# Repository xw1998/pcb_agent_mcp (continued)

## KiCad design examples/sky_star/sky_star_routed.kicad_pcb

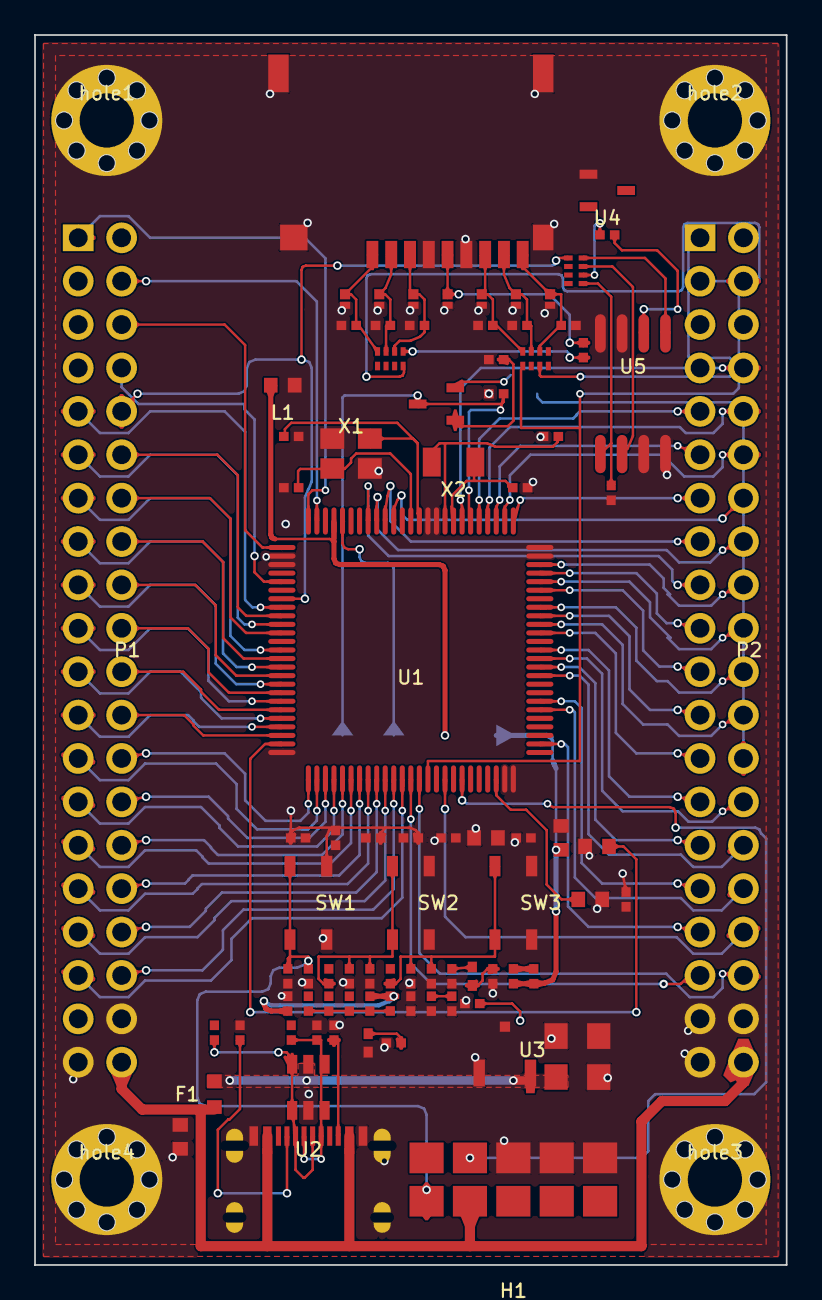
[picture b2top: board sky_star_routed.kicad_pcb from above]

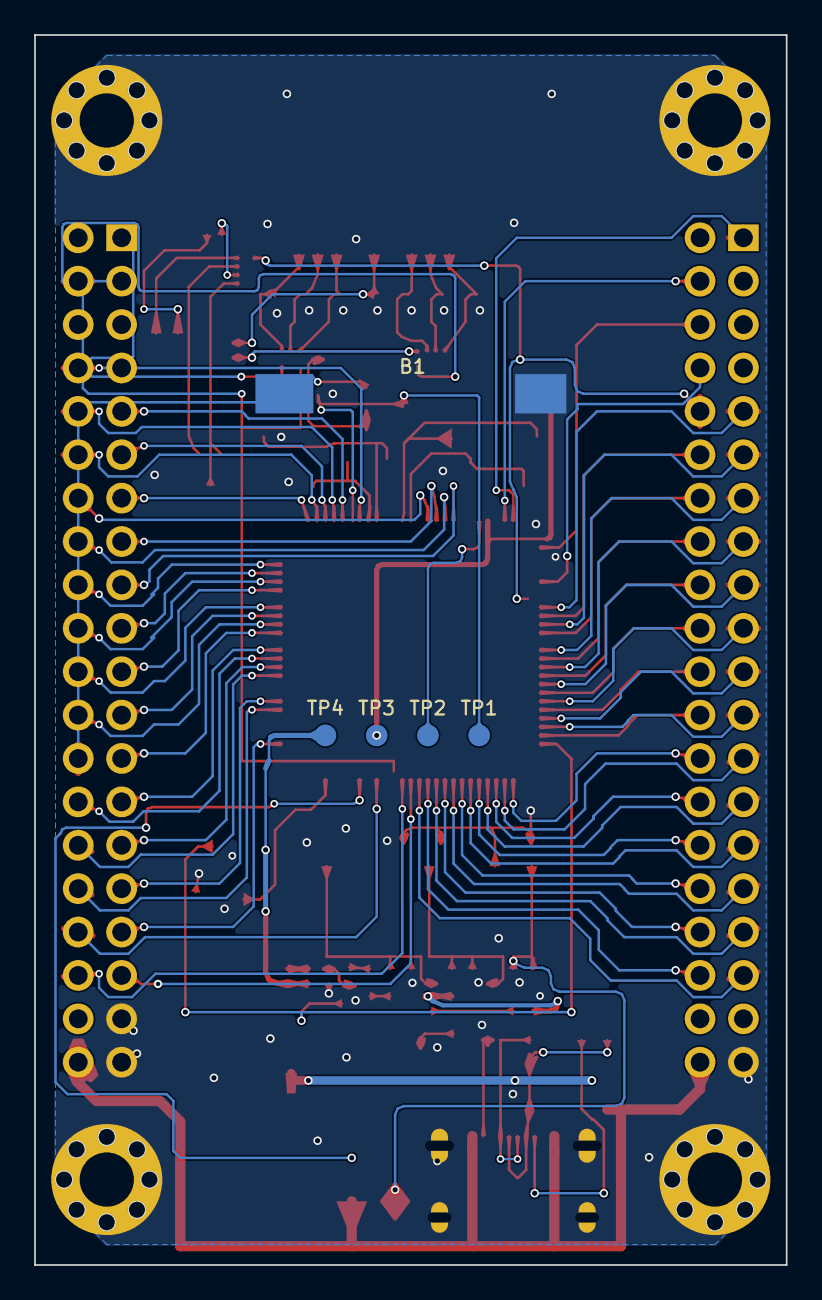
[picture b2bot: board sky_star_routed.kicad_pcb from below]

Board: 2 copper layers, 44.0 x 72.0 mm, 96 parts (5 on the bottom side), 120 nets.

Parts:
B1: 61b387a3f8cf4f8cb9003285; B1
C1: 898d0016e41540f8ae025366; C1
C2: 898d0016e41540f8ae025366; C2
C3: a80f3ac1373c41b29e79f8ac; C3
C4: a80f3ac1373c41b29e79f8ac; C4
C5: ba92d279d25f4ddfba864fc3; C5
C6: 985a7bbf505b401b9df199a7; C6
C7: 985a7bbf505b401b9df199a7; C7
C8: 503038ece5c945bd836f8146; C8
C9: 503038ece5c945bd836f8146; C9
C10: ba92d279d25f4ddfba864fc3; C10
C11: 985a7bbf505b401b9df199a7; C11
C12: 674f7d04ecfe47e19e31325e; C12
C13: 985a7bbf505b401b9df199a7; C13
C14: 985a7bbf505b401b9df199a7; C14
C15: 985a7bbf505b401b9df199a7; C15
C16: 985a7bbf505b401b9df199a7; C16
C17: 985a7bbf505b401b9df199a7; C17
C18: 985a7bbf505b401b9df199a7; C18
C19: c3d1642f07c74a079740bc29; C19
C20: c3d1642f07c74a079740bc29; C20
C21: ed38a11610a64051a2e5fa8d; C21
C22: 674f7d04ecfe47e19e31325e; C22
C23: 985a7bbf505b401b9df199a7; C23
C24: 985a7bbf505b401b9df199a7; C24
C25: 985a7bbf505b401b9df199a7; C25
C26: 985a7bbf505b401b9df199a7; C26
C27: 985a7bbf505b401b9df199a7; C27
CARD1: 0e7a72cfa4f643628d5d1c22; CARD1
D1: d04567a3f4bd40c58faa9031; D1
D2: e103e84b8c7c4680b01127bb; D2
D3: 9a006e8efdae40648d5732ff; D3
D4: 9a006e8efdae40648d5732ff; D4
D5: 9a006e8efdae40648d5732ff; D5
D6: 9a006e8efdae40648d5732ff; D6
D7: 9a006e8efdae40648d5732ff; D7
D8: 9a006e8efdae40648d5732ff; D8
D9: 9a006e8efdae40648d5732ff; D9
F1: b4abf8c794e84f298081ad3d; F1
H1: e0b313ac55d14cdd8e1d890f; H1
L1: c4be498a9b2c478d9cc6793a; L1
LED1: b2f59cdef59d49788923a43d; LED1
LED2: d5cfa2539fc44cb2b9e9363e; LED2
P1: 62604d02a0e44089874c6f57; P1
P2: 62604d02a0e44089874c6f57; P2
R1: 12b2efa1cf58486a9619da63; R1
R2: 12b2efa1cf58486a9619da63; R2
R3: 12b2efa1cf58486a9619da63; R3
R4: ec8dbb3ef10a4b60836874c1; R4
R5: 12b2efa1cf58486a9619da63; R5
R6: 12b2efa1cf58486a9619da63; R6
R7: 12b2efa1cf58486a9619da63; R7
R8: 12b2efa1cf58486a9619da63; R8
R9: 3798b972c8914680bf389273; R9
R10: 7d8c83fa2ece4dc88e778541; R10
R11: 7d8c83fa2ece4dc88e778541; R11
R12: 3798b972c8914680bf389273; R12
R13: d347a19dff4940ed89f0538a; R13
R14: 8adac930023d4a0e80259176; R14
R15: 41c2377d4d534296a53042e6; R15
R16: 41c2377d4d534296a53042e6; R16
R17: 41c2377d4d534296a53042e6; R17
R18: 41c2377d4d534296a53042e6; R18
R19: 41c2377d4d534296a53042e6; R19
R20: 41c2377d4d534296a53042e6; R20
R21: 203e7d3950e0483ab1e27f5d; R21
R22: 8d212afd70d04d809b7d3a37; R22
R23: 203e7d3950e0483ab1e27f5d; R23
R24: faff0499d77046cc8d3395ba; R24
R25: faff0499d77046cc8d3395ba; R25
R26: faff0499d77046cc8d3395ba; R26
R27: faff0499d77046cc8d3395ba; R27
R28: faff0499d77046cc8d3395ba; R28
R29: 8adac930023d4a0e80259176; R29
R30: faff0499d77046cc8d3395ba; R30
RN1: 03d8c6fff59145c59e14821e; RN1
RN2: 03d8c6fff59145c59e14821e; RN2
RN3: 03d8c6fff59145c59e14821e; RN3
SW1: 8a353f60d85b4c9a8f6ee1d9; SW1
SW2: 0186f8a51cea40f9996dc1e2; SW2
SW3: 0186f8a51cea40f9996dc1e2; SW3
TP1: 307121d53d324ab8bbacd7b3; TP1
TP2: 307121d53d324ab8bbacd7b3; TP2
TP3: 307121d53d324ab8bbacd7b3; TP3
TP4: 307121d53d324ab8bbacd7b3; TP4
U1: e9bc99d2d5884074a910997b; U1
U2: 05cba19d26b44aca94b25e1e; U2
U3: dfcfb6bb46c94cd29580c5ab; U3
U4: 13454547d96d49deb0b2d1d6; U4
U5: 0725a72de06845509f1a35bc; U5
X1: 833c1e2704e6450da98a095b; X1
X2: 3dc4ad2b372549639630adff; X2
hole1: b4e398820e034dc2a8638f46; hole1
hole2: b4e398820e034dc2a8638f46; hole2
hole3: b4e398820e034dc2a8638f46; hole3
hole4: b4e398820e034dc2a8638f46; hole4

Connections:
$1I5653/$1N710: C26.2, R25.2, R27.1, SW2.3, SW2.4
$1I5653/$1N718: C27.2, R26.2, R28.1, SW3.3, SW3.4
$1I5653/$1N747: LED2.1, R29.1
$1I7801/$1N957: R11.1, U2.B5
$1I7801/$1N960: R10.1, U2.A5
$1I7801/$1N962: D2.1, D2.6, R9.1, U2.A7, U2.B7
$1I7801/$1N2108: LED1.1, R14.1
$1I7801/$1N8196: D2.3, D2.4, R12.1, R13.1, U2.A6, U2.B6
$1I7895/$1N1161: CARD1.5, D9.1, R21.2
$1I7895/$1N1206: R23.1, U5.6
$1I7895/_SDIO_CLK: R21.1, RN1.4
$1I7895/_SDIO_CMD: CARD1.3, D8.1, R15.1, RN1.3
$1I7895/_SDIO_D0: CARD1.7, D7.1, R16.1, RN2.1
$1I7895/_SDIO_D1: CARD1.8, D6.1, R17.1, RN2.2
$1I7895/_SDIO_D2: CARD1.1, D5.1, R18.1, RN1.1
$1I7895/_SDIO_D3: CARD1.2, D4.1, R19.1, RN1.2
$1I7895/_SD_CARD_DET: CARD1.9, D3.1, R20.1, RN2.3
$1I7895/_SPI_CLK: R23.2, RN3.3
$1I7895/_SPI_CS: R22.1, RN3.4, U5.1
$1I7895/_SPI_MISO: RN3.2, U5.2
$1I7895/_SPI_MOSI: RN3.1, U5.5
$1I8749/$2N1173: C7.1, D1.3, TP1.1, U1.6
$1I8749/$2N1176: D1.1, R3.2
$1I8749/$2N1188: C5.1, C6.2, R1.1, R2.1, R4.1, TP2.1, U1.21
$1I8749/$2N1193: C8.2, U1.73
$1I8749/$2N1197: R5.2, R6.2, U1.19
$1I8749/$2N1200: C9.2, R7.2, U1.49
$1I8749/OSC32_IN: C3.2, U1.8, X2.1
$1I8749/OSC32_OUT: C4.2, U1.9, X2.2
$1I8749/OSC_IN: C2.1, U1.12, X1.3
$1I8749/OSC_OUT: C1.2, U1.13, X1.1
$1I8749/VDDA: C10.2, C11.2, L1.2, R4.2, TP3.1, U1.22
$1N4349: R26.1, U1.94
$1N4351: LED2.2, R30.1, U1.37
$1N4401: H1.8, U1.69
$1N4403: H1.10, U1.68
$1N4405: H1.3, U1.76
$1N4407: H1.5, U1.72
$1N4409: H1.1, U1.89
$1N4415: C25.2, H1.9, R24.2, SW1.3, SW1.4, U1.14
$1N4746: P2.33, U1.77
$1N4748: P1.11, U1.35
$1N4750: P1.14, U1.36
$1N4752: P2.8, U1.7
$1N4754: P2.32, U1.81
$1N4756: P2.31, U1.82
$1N4758: P2.34, U1.67
$1N4760: P1.2, R2.2
$1N4849: P2.4, RN1.5, U1.80
$1N4856: P2.5, RN1.6, U1.83
$1N4863: P2.3, RN2.8, U1.65
$1N4870: P2.2, RN2.7, U1.66
$1N4877: P2.7, RN1.8, U1.78
$1N4884: P2.6, RN1.7, U1.79
$1N4891: P2.1, RN2.6, U1.84
$1N4898: P1.5, RN3.5, U1.29
$1N4905: P1.8, RN3.6, U1.30
$1N4912: P1.7, RN3.7, U1.31
$1N4919: P1.10, RN3.8, U1.32
$1N5556: R1.2, U4.2
$1N5560: R9.2, U1.70
$1N5562: R12.2, U1.71
$1N8183: P1.3, R25.1, U1.23
$1N9171: B1.1, D1.2, P2.26
+3V3: C12.2, C13.2, C14.2, C15.2, C16.2, C17.2, C18.2, C20.1, C21.2, C22.1, C23.1, C24.2, C26.1, C27.1, CARD1.4, H1.2, L1.1, LED1.2, P1.38, P2.38, R3.1, R5.1, R13.2, R15.2, R16.2, R17.2, R18.2, R19.2, R20.2, R22.2, R24.1, SW2.1, SW2.2, SW3.1, SW3.2, U1.11, U1.28, U1.50, U1.75, U1.100, U3.2, U4.1, U5.3, U5.7, U5.8
+5V: C19.1, D2.5, F1.2, U3.3
AGND: C5.2, C6.1, C10.1, C11.1, C21.1, P1.37, R8.1, TP4.1, U1.20, U4.3
GND: B1.2, C1.1, C2.2, C3.1, C4.1, C7.2, C8.1, C9.1, C12.1, C13.1, C14.1, C15.1, C16.1, C17.1, C18.1, C19.2, C20.2, C22.2, C23.2, C24.1, C25.1, CARD1.6, CARD1.10, CARD1.11, CARD1.12, CARD1.13, D2.2, D3.2, D4.2, D5.2, D6.2, D7.2, D8.2, D9.2, H1.4, H1.6, P1.39, P2.37, P2.39, R6.1, R7.1, R8.2, R10.2, R11.2, R14.2, R27.2, R28.2, R29.2, R30.2, SW1.1, SW1.2, U1.10, U1.27, U1.74, U1.99, U2.1, U2.2, U2.3, U2.4, U2.A1B12, U2.A12B1, U3.1, U5.4, X1.2, X1.4, hole1.1, hole2.1, hole3.1, hole4.1
PA1: P1.4, U1.24
PA2: P1.1, U1.25
PA3: P1.6, U1.26
PB4: P2.25, U1.90
PB5: P2.24, U1.91
PB6: P2.23, U1.92
PB7: P2.22, U1.93
PB8: P2.21, U1.95
PB9: P2.20, U1.96
PB10: P1.23, U1.47
PB11: P1.24, U1.48
PB12: P1.26, U1.51
PB13: P1.25, U1.52
PB14: P1.28, U1.53
PB15: P1.27, U1.54
PC0: P2.14, U1.15
PC1: P2.15, U1.16
PC2: P2.16, U1.17
PC3: P2.17, U1.18
PC4: P1.9, U1.33
PC5: P1.12, U1.34
PC6: P2.35, U1.63
PC7: P2.36, U1.64
PD4: P2.30, U1.85
PD5: P2.29, U1.86
PD6: P2.28, U1.87
PD7: P2.27, U1.88
PD8: P1.30, U1.55
PD9: P1.29, U1.56
PD10: P1.32, U1.57
PD11: P1.31, U1.58
PD12: P1.34, U1.59
PD13: P1.33, U1.60
PD14: P1.36, U1.61
PD15: P1.35, U1.62
PE0: P2.19, U1.97
PE1: P2.18, U1.98
PE2: P2.13, U1.1
PE3: P2.12, U1.2
PE4: P2.11, U1.3
PE5: P2.10, U1.4
PE6: P2.9, U1.5
PE7: P1.13, U1.38
PE8: P1.16, U1.39
PE9: P1.15, U1.40
PE10: P1.18, U1.41
PE11: P1.17, U1.42
PE12: P1.20, U1.43
PE13: P1.19, U1.44
PE14: P1.22, U1.45
PE15: P1.21, U1.46
PIN_IN_+5V: F1.1, H1.7, P1.40, P2.40, U2.A4B9, U2.A9B4

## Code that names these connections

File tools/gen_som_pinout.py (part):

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EDGES = {
    # ---- N：RGB LCDC 28 信号（VO_LCDC_D0..D23 + CLK/HSYNC/VSYNC/DEN）
    "N": [
        ("sig", "G3", "LCDC_D0", "GPIO1/LCDC"),
        ("sig", "F2", "LCDC_D1", "GPIO1/LCDC"),
        ("sig", "F3", "LCDC_D2", "GPIO1/LCDC"),
        ("sig", "E1", "LCDC_D3", "GPIO1/LCDC"),
        ("sig", "E2", "LCDC_D4", "GPIO1/LCDC"),
        ("sig", "E3", "LCDC_D5", "GPIO1/LCDC"),
        ("sig", "D3", "LCDC_D6", "GPIO1/LCDC"),
        ("sig", "C1", "LCDC_D7", "GPIO1/LCDC"),
        ("GND",),
        ("sig", "C2", "LCDC_D8", "GPIO1/LCDC"),
        ("sig", "B1", "LCDC_D9", "GPIO1/LCDC"),
        ("sig", "B2", "LCDC_D10", "GPIO1/LCDC"),
        ("sig", "A2", "LCDC_D11", "GPIO1/LCDC"),
        ("sig", "B3", "LCDC_D12", "GPIO1/LCDC"),
        ("sig", "A3", "LCDC_D13", "GPIO1/LCDC"),
        ("GND",),
        ("sig", "C3", "LCDC_D14", "GPIO1/LCDC"),
        ("sig", "1A1", "LCDC_D15", "GPIO1/LCDC"),
        ("sig", "B5", "LCDC_D16", "GPIO1/LCDC"),
        ("sig", "A5", "LCDC_D17", "GPIO1/LCDC"),
        ("sig", "1A2", "LCDC_D18", "GPIO1/LCDC"),
        ("sig", "1A3", "LCDC_D19", "GPIO1/LCDC"),
        ("GND",),
        ("sig", "B7", "LCDC_D20", "GPIO1/LCDC"),
        ("sig", "A7", "LCDC_D21", "GPIO1/LCDC"),
        ("sig", "1A4", "LCDC_D22", "GPIO1/LCDC"),
        ("sig", "B8", "LCDC_D23", "GPIO1/LCDC"),
        ("sig", "B9", "LCDC_CLK", "GPIO1/LCDC"),
        ("GND",),
        ("sig", "A9", "LCDC_HSYNC", "GPIO1/LCDC"),
        ("sig", "1A5", "LCDC_VSYNC", "GPIO1/LCDC"),
        ("sig", "B10", "LCDC_DEN", "GPIO1/LCDC"),
    ],
    # ---- E：MIPI DSI + USB + SARADC + ACODEC + 5V 输入
    "E": [
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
